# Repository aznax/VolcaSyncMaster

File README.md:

# VolcaSyncMaster
Volca Sync master - 1 in 8 out Volca Sync Master

Having but two hands and several volcas i find it hard to be able to actively play more than one or two at time in time, then it struck
me that it might be handy to able to sequence the start of the sync pulses, then it struck me that it would be handy to be able to sequence 
the starting and stopping of the sequences, kind of like a ultra active step. cool right?

## and...well here we are.

Still in early phase, looking at using the [cy8ckit-059-LP](https://www.cypress.com/documentation/development-kitsboards/cy8ckit-059-psoc-5lp-prototyping-kit-onboard-programmer-and) to act as a master volca Sync for sequencable sync signals for up to 
8 korg volcas. ideally being able to send sync out at a range of sync divisions 

- 1/1 (full BPM)
- 1/2 (half BPM)
- 1/4 (quarter BPM)
- 1/8 (you get the idea)

and also worthwhile might be being able to sequence the sync pulses 

- every step (standard) 
- play 8 wait 8 
- play 4 wait 4
- play 12 wait 4
- wait 4 play 4
- play 16 wait 16

## But...

before being able to get there i need to design the circuit to handle the sync pulses in and out, having a drawer full of dev boards, 
of all shapes and sizes, I settled on the Cypress CY8CKIT-059-LP as being low cost, has robust configurable IO options.

## Docs

The resources docs for this project are published by the respective companies, Cypress, Korg, and others, and wont be included here.

### slowly slowly catchy monkey

The time frame for this project is undefined and will need to fit in between life, work and study, and actually playing the volcas, and learning how to kicad and program, but it's still rolling along when i get a chance.

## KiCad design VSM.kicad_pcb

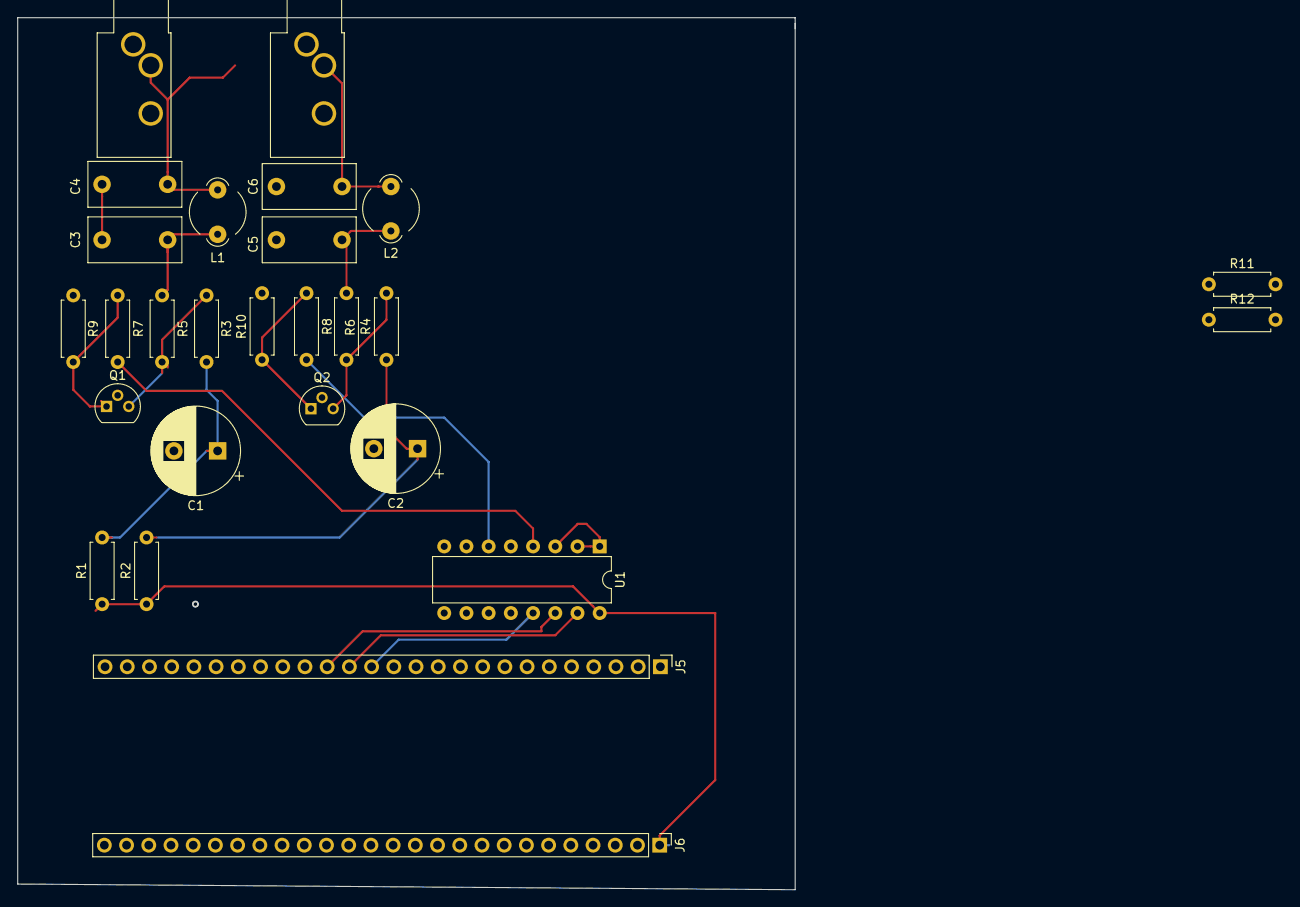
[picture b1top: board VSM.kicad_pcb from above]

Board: 2 copper layers, 88.9 x 99.7 mm, 27 parts (0 on the bottom side), 21 nets.

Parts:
C1, C2: 1u; CP_Radial_D10.0mm_P5.00mm
C3, C4, C5, C6: 1000p; C_Disc_D10.5mm_W5.0mm_P7.50mm
J1, J2: Sync Worker 1; Jack_3.5mm_CUI_SJ1-3533NG_Horizontal_CircularHoles
J5, J6: Conn_01x26_Female; PinHeader_1x26_P2.54mm_Vertical
L1, L2: 961Ω impedance at 100 MHz; LairdTech_28C0236-0JW-10
Q1, Q2: 2N5210; TO-92
R1, R2: 4.7k; R_Axial_DIN0207_L6.3mm_D2.5mm_P7.62mm_Horizontal
R3, R4: 470; R_Axial_DIN0207_L6.3mm_D2.5mm_P7.62mm_Horizontal
R5, R6: 1k; R_Axial_DIN0207_L6.3mm_D2.5mm_P7.62mm_Horizontal
R7, R8: 10k; R_Axial_DIN0207_L6.3mm_D2.5mm_P7.62mm_Horizontal
R9, R10: 100k; R_Axial_DIN0207_L6.3mm_D2.5mm_P7.62mm_Horizontal
R11, R12: 330; R_Axial_DIN0207_L6.3mm_D2.5mm_P7.62mm_Horizontal
U1: PCF8574A; DIP-16_W7.62mm

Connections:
/AD_L: U1.1, U1.2, U1.3
/P2_5: J5.6, J6.6
/P12_2: J5.14, U1.13
/SCL: J5.16, U1.14
/SDA: J5.15, U1.15
/Sync_m_1: R7.2, U1.4
/Sync_m_2: R11.1, U1.5
/Sync_m_3: R8.2, U1.6
/Sync_m_4: R12.1, U1.7
GND: C1.2, C2.2, C3.2, C4.2, C5.2, C6.2, J1.S, J2.S, J5.25, J6.2, J6.26, Q1.2, Q2.2, R9.2, R10.2, U1.8
unnamed: C1.1, R1.2, R3.1
unnamed: C2.1, R2.2, R4.1
unnamed: C3.1, L1.2, R5.1
unnamed: C4.1, J1.T, L1.1
unnamed: C5.1, L2.2, R6.1
unnamed: C6.1, J2.T, L2.1
unnamed: Q1.1, R7.1, R9.1
unnamed: Q1.3, R3.2, R5.2
unnamed: Q2.1, R8.1, R10.1
unnamed: Q2.3, R4.2, R6.2
VDD: J6.1, R1.1, R2.1, U1.16

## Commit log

2019-09-16 Add files via upload
    Files for upload
